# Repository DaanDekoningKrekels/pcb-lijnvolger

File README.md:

# PCB Lijnvolger

## Snelle links

- [Opdrachtomschrijving](./oo2-opdrachtbeschrijving.pdf)
- [Onderzoeksdocument](./onderzoeksdocument.md)
- [PCB-ontwerp](./src/kicad-project/)
- [Testplan bestukken printplaat](testplan.md)

## Project structuur

```
.
├── assets                  (figuren)
├── datasheets              (datasheets gebruikte componenten)
└── src                     (alle bronbestanden)
    ├── kicad-project       (PCB-ontwerp)
    ├── LEDD0-test          (test voor LED Drivers)
    ├── SENSE-0-1-test      (test voor eerste sensoren)
    ├── TinyLijnvolger      (finale code)
    └── WIRE-test           (test voor I2C verbinding)
```

## Verslag PCB-lijnvolger

In deze repository kan alle informatie teruggevonden worden rond dit project.

Het onderzoeksdocument beschrijft de algemene verwachtingen voor dit project en hoe ik van plan was het aan te pakken. Ik denk dat het onderzoek vrij goed aansluit met hoe het project uiteindelijk is verlopen. Het jammere is dat ik de meeste code niet heb kunnen testen omdat I2C niet werkt. Dit is echter een softwareprobleem en ligt niet aan het ontwerp van de printplaat.

Zo zou de PCB eruit zien:

Dit is hoe de definitieve printplaat eruit ziet:

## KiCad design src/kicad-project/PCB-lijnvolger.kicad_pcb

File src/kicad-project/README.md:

## Schema lijnvolger

## PCB lijnvolger

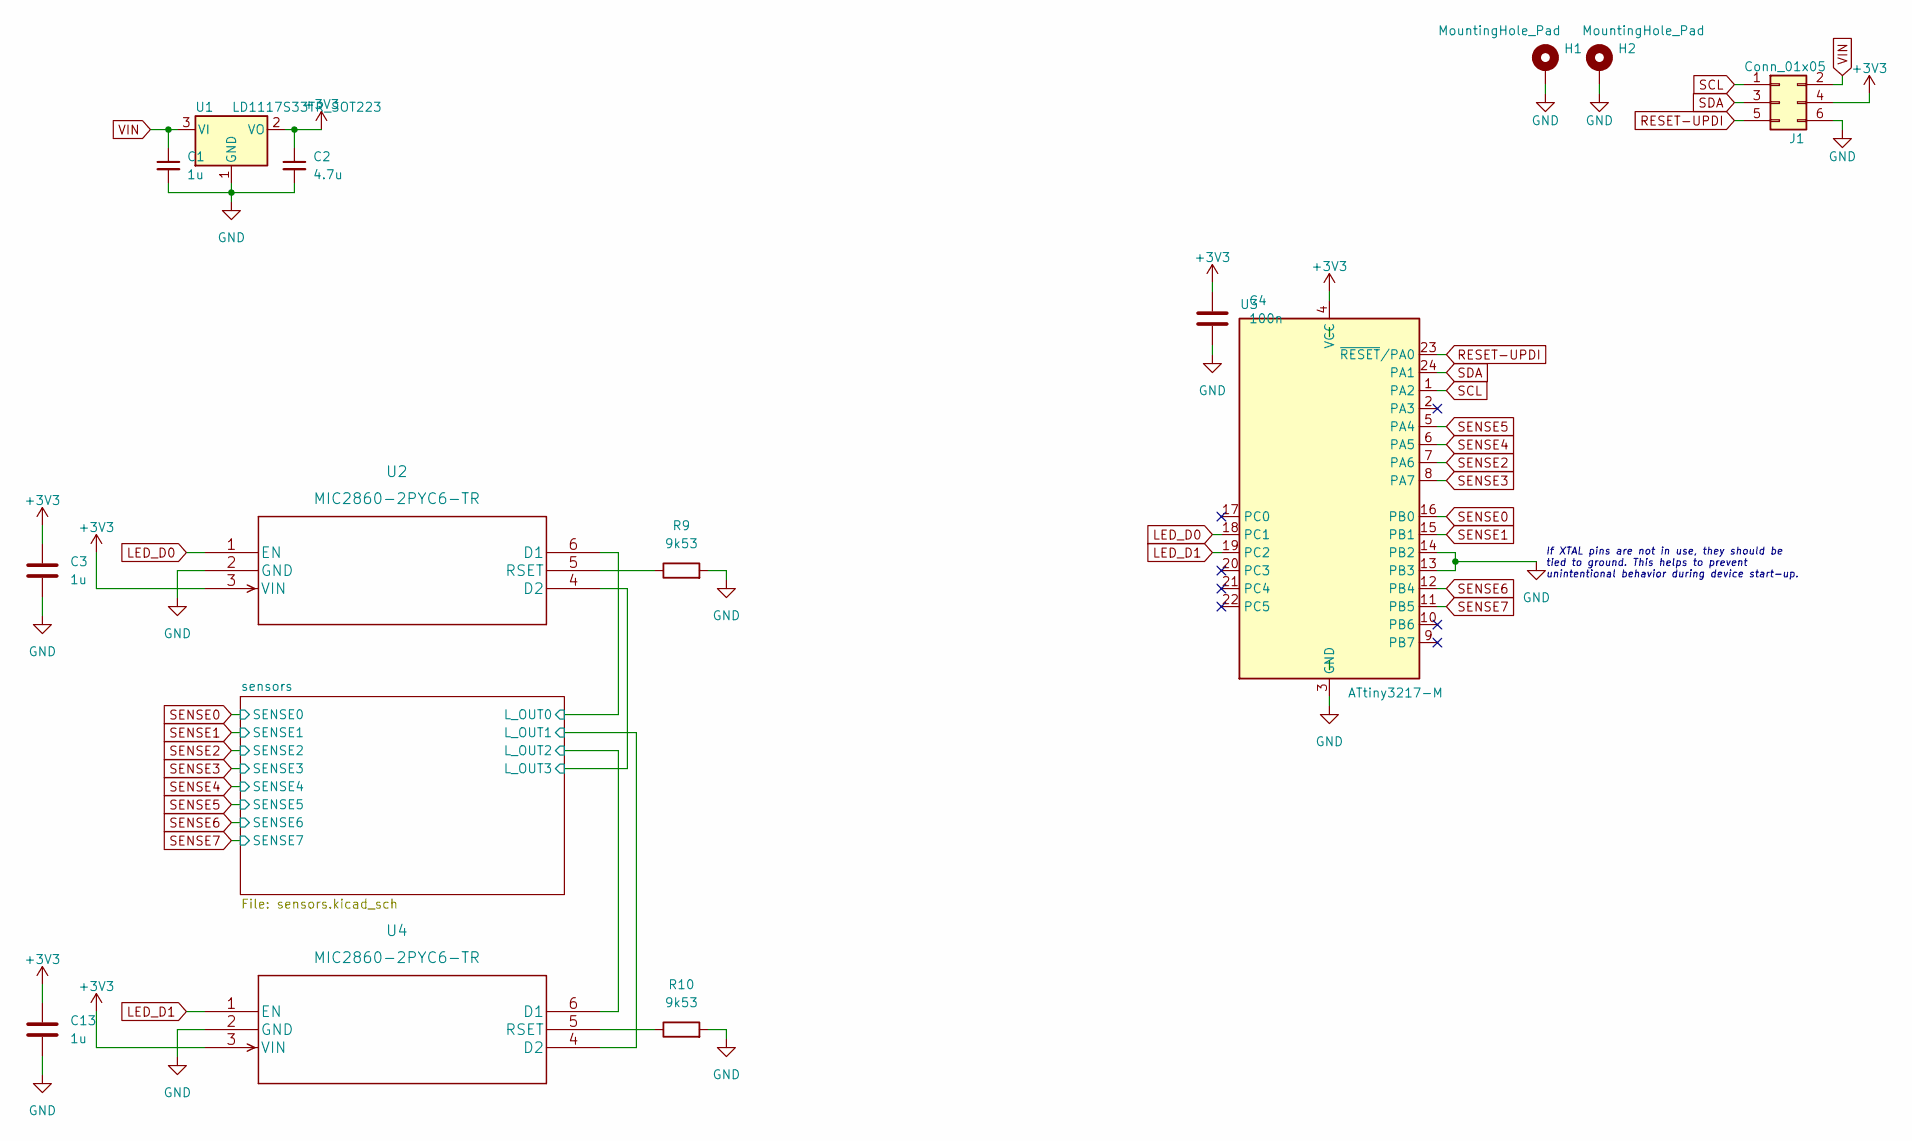
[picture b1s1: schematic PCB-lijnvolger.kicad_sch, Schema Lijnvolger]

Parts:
C1, C3, C13: 1u; C_0805_2012Metric_Pad1.18x1.45mm_HandSolder
C2: 4.7u; C_0805_2012Metric_Pad1.18x1.45mm_HandSolder
C4: 100n; C_0805_2012Metric_Pad1.18x1.45mm_HandSolder
H1, H2: MountingHole_Pad; MountingHole_2.5mm_Pad
J1: Conn_01x05; PinHeader_2x03_P2.54mm_Vertical
R9, R10: 9k53; R_0805_2012Metric_Pad1.20x1.40mm_HandSolder
U1: LD1117S33TR_SOT223; SOT-223-3_TabPin2
U2, U4: MIC2860-2PYC6-TR; SOT-23-6_Handsoldering
U3: ATtiny3217-M; QFN-24-1EP_4x4mm_P0.5mm_EP2.6x2.6mm

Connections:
+3V3: C2.1, C3.1, C4.1, C13.1, J1.4, U1.2 (VO), U2.3 (VIN), U3.4 (VCC), U4.3 (VIN); also elsewhere on the board
/sensors/L_OUT0: U2.6 (D1); also elsewhere on the board
/sensors/L_OUT1: U4.4 (D2); also elsewhere on the board
/sensors/L_OUT2: U4.6 (D1); also elsewhere on the board
/sensors/L_OUT3: U2.4 (D2); also elsewhere on the board
GND: C1.2, C2.2, C3.2, C4.2, C13.2, H1.1, H2.1, J1.6, R9.2, R10.2, U1.1 (GND), U2.2 (GND), U3.3 (GND), U3.13 (PB3), U3.14 (PB2), U3.25 (GND), U4.2 (GND); also elsewhere on the board
LED_D0: U2.1 (EN), U3.18 (PC1)
LED_D1: U3.19 (PC2), U4.1 (EN)
unnamed: R9.1, U2.5 (RSET)
unnamed: R10.1, U4.5 (RSET)
RESET-UPDI: J1.5, U3.23 (~RESET/PA0)
SCL: J1.1, U3.1 (PA2)
SDA: J1.3, U3.24 (PA1)
SENSE0: U3.16 (PB0); also elsewhere on the board
SENSE1: U3.15 (PB1); also elsewhere on the board
SENSE2: U3.7 (PA6); also elsewhere on the board
SENSE3: U3.8 (PA7); also elsewhere on the board
SENSE4: U3.6 (PA5); also elsewhere on the board
SENSE5: U3.5 (PA4); also elsewhere on the board
SENSE6: U3.12 (PB4); also elsewhere on the board
SENSE7: U3.11 (PB5); also elsewhere on the board
VIN: C1.1, J1.2, U1.3 (VI)

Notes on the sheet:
If XTAL pins are not in use, they should be tied to ground. This helps to prevent unintentional behavior during device start-up.

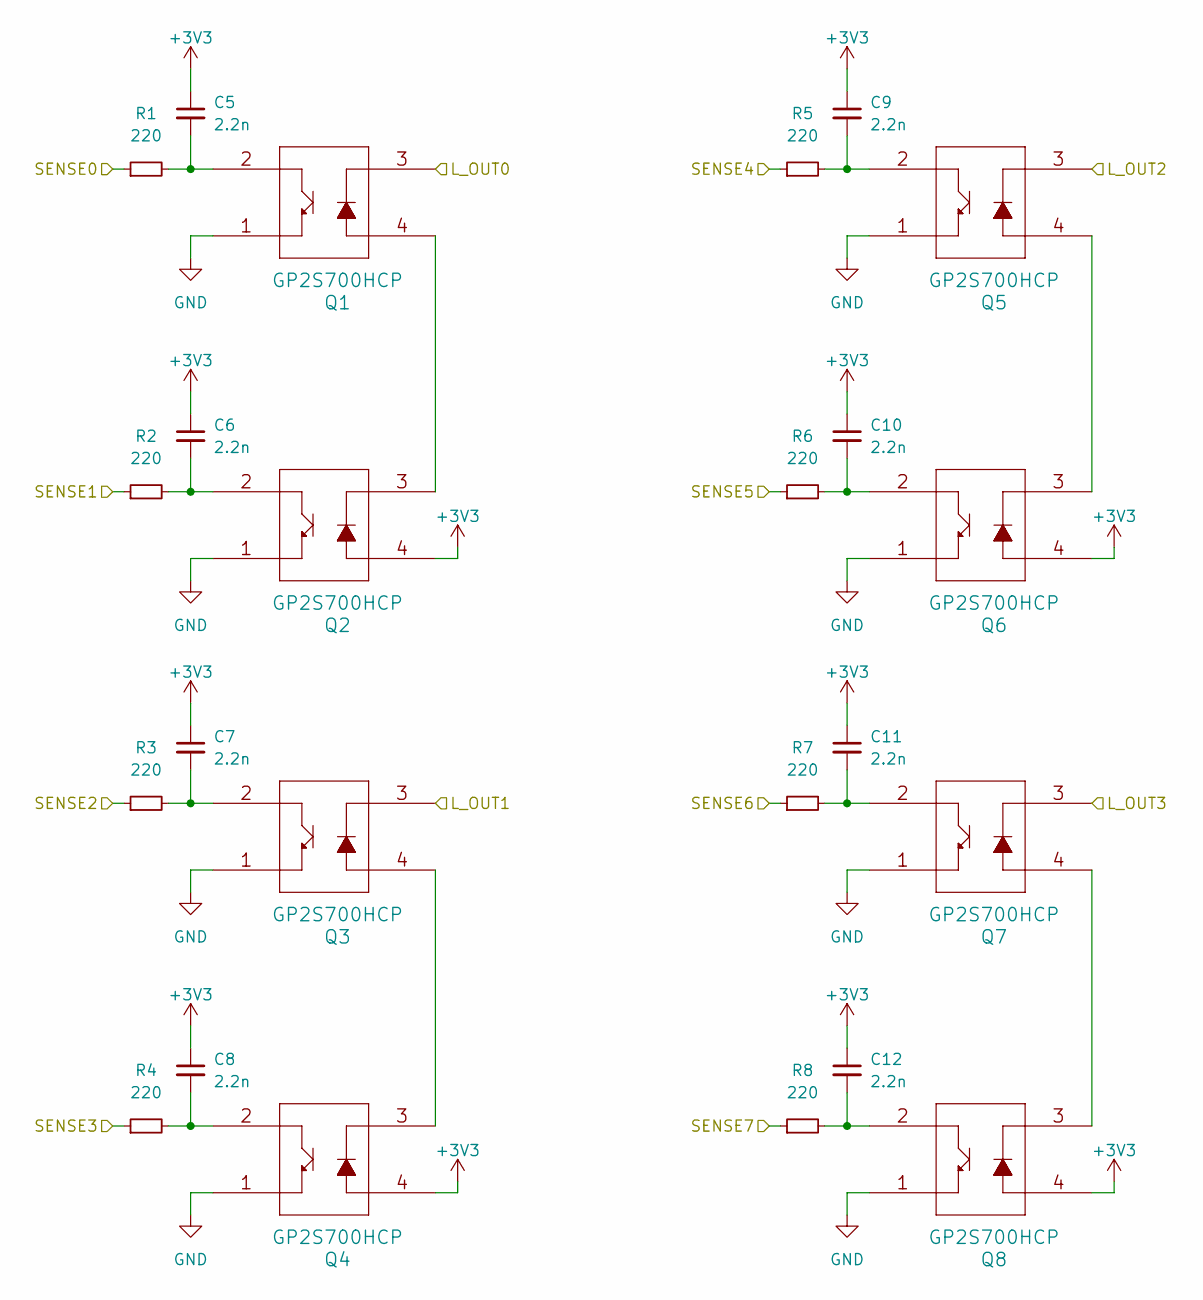
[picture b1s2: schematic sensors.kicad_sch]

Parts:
C5, C6, C7, C8, C9, C10, C11, C12: 2.2n; C_0805_2012Metric_Pad1.18x1.45mm_HandSolder
Q1, Q2, Q3, Q4, Q5, Q6, Q7, Q8: GP2S700HCP
R1, R2, R3, R4, R5, R6, R7, R8: 220; R_0805_2012Metric_Pad1.20x1.40mm_HandSolder

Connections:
+3V3: C5.1, C6.1, C7.1, C8.1, C9.1, C10.1, C11.1, C12.1, Q2.4, Q4.4, Q6.4, Q8.4; also elsewhere on the board
/sensors/L_OUT0: Q1.3; also elsewhere on the board
/sensors/L_OUT1: Q3.3; also elsewhere on the board
/sensors/L_OUT2: Q5.3; also elsewhere on the board
/sensors/L_OUT3: Q7.3; also elsewhere on the board
GND: Q1.1, Q2.1, Q3.1, Q4.1, Q5.1, Q6.1, Q7.1, Q8.1; also elsewhere on the board
unnamed: C5.2, Q1.2, R1.2
unnamed: C6.2, Q2.2, R2.2
unnamed: C7.2, Q3.2, R3.2
unnamed: C8.2, Q4.2, R4.2
unnamed: C9.2, Q5.2, R5.2
unnamed: C10.2, Q6.2, R6.2
unnamed: C11.2, Q7.2, R7.2
unnamed: C12.2, Q8.2, R8.2
unnamed: Q1.4, Q2.3
unnamed: Q3.4, Q4.3
unnamed: Q5.4, Q6.3
unnamed: Q7.4, Q8.3
SENSE0: R1.1; also elsewhere on the board
SENSE1: R2.1; also elsewhere on the board
SENSE2: R3.1; also elsewhere on the board
SENSE3: R4.1; also elsewhere on the board
SENSE4: R5.1; also elsewhere on the board
SENSE5: R6.1; also elsewhere on the board
SENSE6: R7.1; also elsewhere on the board
SENSE7: R8.1; also elsewhere on the board

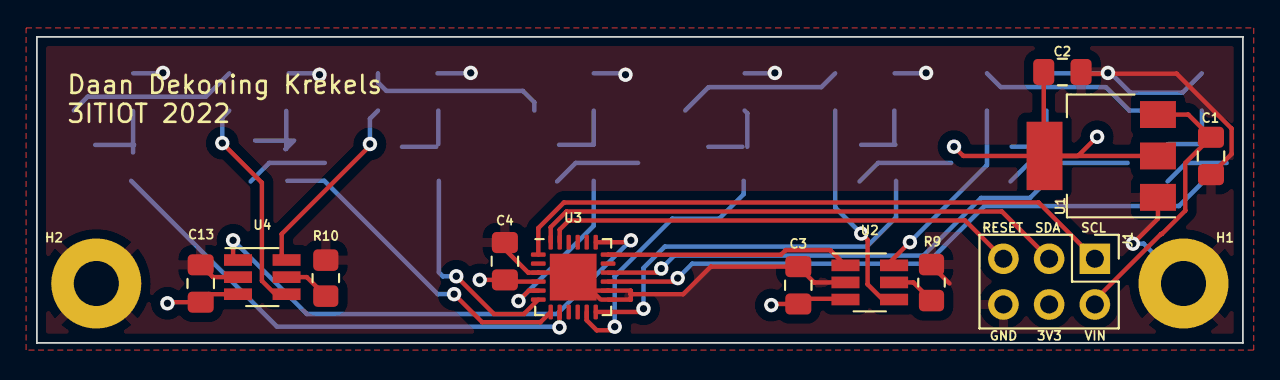
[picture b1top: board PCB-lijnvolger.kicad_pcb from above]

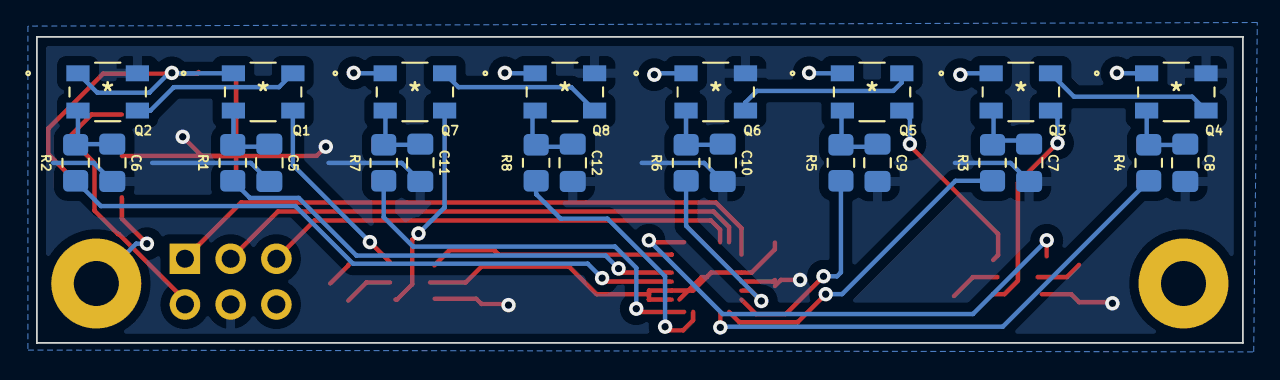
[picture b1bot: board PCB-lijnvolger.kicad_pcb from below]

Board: 2 copper layers, 67.0 x 17.0 mm, 38 parts (24 on the bottom side), 34 nets.

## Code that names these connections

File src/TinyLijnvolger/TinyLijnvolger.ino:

#include <Wire.h>


#define LEDD0 PIN_PC1  // PC1
#define LEDD1 PIN_PC2  // PC2

#define AANTAL_SENSE_PINS 8
#define SENSE0 PIN_PB0  // PB0
#define SENSE1 PIN_PB1  // PB1
#define SENSE2 PIN_PA6  // PA6
#define SENSE3 PIN_PA7  // PA7
#define SENSE4 PIN_PA5  // PA5
#define SENSE5 PIN_PA4  // PA4
#define SENSE6 PIN_PB4  // PB4
#define SENSE7 PIN_PB5  // PB5

const byte SENSE_PINS[AANTAL_SENSE_PINS] = { SENSE0, SENSE1, SENSE2, SENSE3, SENSE4, SENSE5, SENSE6, SENSE7 };
char readings_to_send[AANTAL_SENSE_PINS];

// De master kan verschillende werkingsmodi selecteren door een byte te sturen
// de FAST modi verbruiken meer stroom omdat de IR LED's daar altijd aan staan
// ANALOG stuurt een byte met de analoge waarde van de fotointerruptor
// DIGITAL stuurt een byte met 1 of 0
enum STATES { IDLE,
              FAST_DIGITAL,
              FAST_ANALOG,
              ANALOG,
              DIGITAL };
STATES current_state = IDLE;
STATES new_state = IDLE;

void setup() {
  pinMode(LEDD0, OUTPUT);
  pinMode(LEDD1, OUTPUT);
  for (byte i = 0; i < AANTAL_SENSE_PINS; i++) {
    pinMode(SENSE_PINS[i], INPUT);
  }

  Wire.pins(PIN_PA1, PIN_PA2);
  Wire.begin(0x55);                 // join i2c bus met adres 0x55
  Wire.onRequest(requestEvent);     // register event
  Wire.onReceive(receiveNewState);  // give the Wire library the name of the function
}

void loop() {
  if (new_state != current_state) {
    switch (new_state) {
      case FAST_ANALOG:
        digitalWrite(LEDD0, LOW);  // IR LEDS gaan aan
        digitalWrite(LEDD1, LOW);  // IR LEDS gaan aan

        break;
      case FAST_DIGITAL:
        digitalWrite(LEDD0, LOW);  // IR LEDS gaan aan
        digitalWrite(LEDD1, LOW);  // IR LEDS gaan aan

        break;
      case ANALOG:
        digitalWrite(LEDD0, HIGH);  // IR LEDS gaan uit
        digitalWrite(LEDD1, HIGH);  // IR LEDS gaan uit

        break;
      case DIGITAL:
        digitalWrite(LEDD0, HIGH);  // IR LEDS gaan uit
        digitalWrite(LEDD1, HIGH);  // IR LEDS gaan uit
        break;
      default:
        break;
    }
    current_state = new_state;
  }

  delay(1);
}

bool prepare_readings() {
  switch (new_state) {
    case FAST_ANALOG:
      read_pins_analog_fast();
      return true;
      break;
    case FAST_DIGITAL:
      read_pins_digital_fast();
      return true;
      break;
    case ANALOG:
      read_pins_analog();
      return true;
      break;
    case DIGITAL:
      read_pins_digital();
      return true;
      break;
    default:
      return false;
      ;
  }
}

void read_pins_analog_fast() {
    readings_to_send[0] = (char)analogRead(SENSE_PINS[0]);
    readings_to_send[1] = (char)analogRead(SENSE_PINS[1]);
    readings_to_send[2] = (char)analogRead(SENSE_PINS[2]);
    readings_to_send[3] = (char)analogRead(SENSE_PINS[3]);
    readings_to_send[4] = (char)analogRead(SENSE_PINS[4]);
    readings_to_send[5] = (char)analogRead(SENSE_PINS[5]);
    readings_to_send[6] = (char)analogRead(SENSE_PINS[6]);
    readings_to_send[7] = (char)analogRead(SENSE_PINS[7]);
}

// Idealiter maakt deze functie één byte met iedere bit de waarde van een pin
void read_pins_digital_fast() {
    readings_to_send[0] = (char)digitalRead(SENSE_PINS[0]);
    readings_to_send[1] = (char)digitalRead(SENSE_PINS[1]);
    readings_to_send[2] = (char)digitalRead(SENSE_PINS[2]);
    readings_to_send[3] = (char)digitalRead(SENSE_PINS[3]);
    readings_to_send[4] = (char)digitalRead(SENSE_PINS[4]);
    readings_to_send[5] = (char)digitalRead(SENSE_PINS[5]);
    readings_to_send[6] = (char)digitalRead(SENSE_PINS[6]);
    readings_to_send[7] = (char)digitalRead(SENSE_PINS[7]);
}

void read_pins_analog() {
  digitalWrite(LEDD0, LOW);  // IR LEDS gaan aan
  digitalWrite(LEDD1, LOW);  // IR LEDS gaan aan
  delay(10);

  for (byte i = 0; i < AANTAL_SENSE_PINS; i++) {
    readings_to_send[i] = (char)analogRead(SENSE_PINS[i]);
  }

  delay(10);
  digitalWrite(LEDD0, HIGH);  // IR LEDS gaan uit
  digitalWrite(LEDD1, HIGH);  // IR LEDS gaan uit
}

// Idealiter maakt deze functie één byte met iedere bit de waarde van een pin
void read_pins_digital() {
  digitalWrite(LEDD0, LOW);  // IR LEDS gaan aan
  digitalWrite(LEDD1, LOW);  // IR LEDS gaan aan
  delay(10);

  for (byte i = 0; i < AANTAL_SENSE_PINS; i++) {
    readings_to_send[i] = (char)digitalRead(SENSE_PINS[i]);
  }

  delay(10);
  digitalWrite(LEDD0, HIGH);  // IR LEDS gaan uit
  digitalWrite(LEDD1, HIGH);  // IR LEDS gaan uit
}

// Aanvraag voor de waarde van de fotointerrupters
void requestEvent() {
  if (prepare_readings()){
    Wire.print(readings_to_send);  // respond with message of 8 bytes
  }else{
    Wire.write(0x00);
  }
}

// Wanneer de master een nieuwe status doorgeeft
void receiveNewState(int16_t numBytes) {  // the Wire API tells us how many bytes
  if (numBytes == 1) {
    new_state = STATES(Wire.read());
  }
}

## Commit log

2022-12-20 projectbestanden lijnvolger
2022-12-20 verduidelijking schema en pcb in kicad map
2023-01-08 Toevoegingen voor finale oplevering

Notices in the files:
parts and their libraries:
Copyright 2021 Accelerated Designs. All rights reserved.
